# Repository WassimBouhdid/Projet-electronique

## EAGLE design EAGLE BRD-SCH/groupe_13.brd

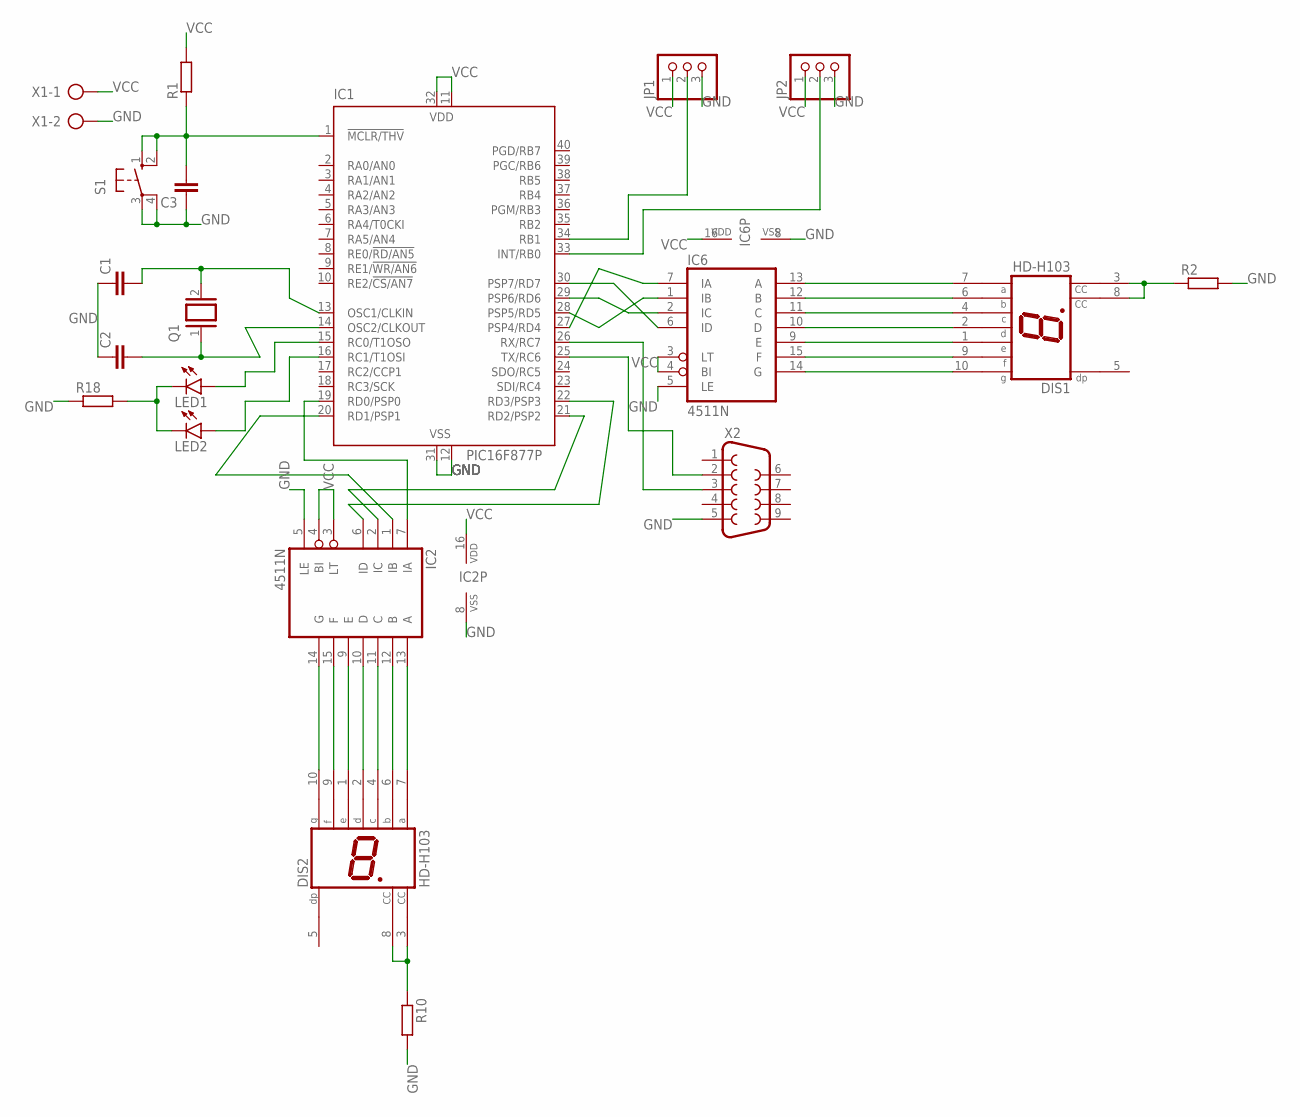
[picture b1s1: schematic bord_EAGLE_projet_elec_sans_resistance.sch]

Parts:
C1, C2: C-EU025-025X050; C025-025X050
C3: C-EU025-024X044; C025-024X044
DIS1, DIS2: HD-H103; HDSP-M
IC1: PIC16F877P; DIL40
IC2, IC6: 4511N; DIL16
JP1, JP2: PINHD-1X3; 1X03
LED1, LED2: LED5MM
Q1: XTAL/S; QS
R1, R2, R10, R18: R-EU_0204/7; 0204/7
S1: 10-XX; B3F-10XX
X1: AK300/2
X2: F09H

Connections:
GND: C1.1, C2.1, C3.1, IC1.12 (VSS), IC1.31 (VSS), IC2.5 (LE), IC2.8 (VSS), IC6.5 (LE), IC6.8 (VSS), JP1.3, JP2.3, R2.2, R10.2, R18.1, S1.3, S1.4 (P1), X1.2, X2.5
unnamed: C1.2, IC1.13 (OSC1/CLKIN), Q1.2
unnamed: C2.2, IC1.14 (OSC2/CLKOUT), Q1.1
unnamed: C3.2, IC1.1 (!MCLR/THV), R1.1, S1.1 (S), S1.2 (S1)
unnamed: IC1.19 (RD0/PSP0), IC2.7 (IA)
unnamed: IC1.20 (RD1/PSP1), IC2.1 (IB)
unnamed: IC1.21 (RD2/PSP2), IC2.2 (IC)
unnamed: IC1.22 (RD3/PSP3), IC2.6 (ID)
unnamed: IC1.27 (PSP4/RD4), IC6.7 (IA)
unnamed: IC1.28 (PSP5/RD5), IC6.1 (IB)
unnamed: IC1.29 (PSP6/RD6), IC6.2 (IC)
unnamed: IC1.30 (PSP7/RD7), IC6.6 (ID)
unnamed: DIS1.7 (A), IC6.13 (A)
unnamed: DIS1.6 (B), IC6.12 (B)
unnamed: DIS1.4 (C), IC6.11 (C)
unnamed: DIS1.2 (D), IC6.10 (D)
unnamed: DIS1.1 (E), IC6.9 (E)
unnamed: DIS1.9 (F), IC6.15 (F)
unnamed: DIS1.10 (G), IC6.14 (G)
unnamed: DIS2.10 (G), IC2.14 (G)
unnamed: DIS2.9 (F), IC2.15 (F)
unnamed: DIS2.1 (E), IC2.9 (E)
unnamed: DIS2.2 (D), IC2.10 (D)
unnamed: DIS2.4 (C), IC2.11 (C)
unnamed: DIS2.6 (B), IC2.12 (B)
unnamed: DIS2.7 (A), IC2.13 (A)
unnamed: DIS1.3 (CC), DIS1.8 (CC), R2.1
unnamed: DIS2.3 (CC), DIS2.8 (CC), R10.1
unnamed: IC1.15 (RC0/T1OSO), LED1.A
unnamed: IC1.16 (RC1/T1OSI), LED2.A
unnamed: LED1.K (C), LED2.K (C), R18.2
unnamed: IC1.25 (TX/RC6), X2.2
unnamed: IC1.26 (RX/RC7), X2.3
unnamed: IC1.33 (INT/RB0), JP2.2
unnamed: IC1.34 (RB1), JP1.2
VCC: IC1.11 (VDD), IC1.32 (VDD), IC2.3 (LT), IC2.4 (BI), IC2.16 (VDD), IC6.3 (LT), IC6.4 (BI), IC6.16 (VDD), JP1.1, JP2.1, R1.2, X1.1

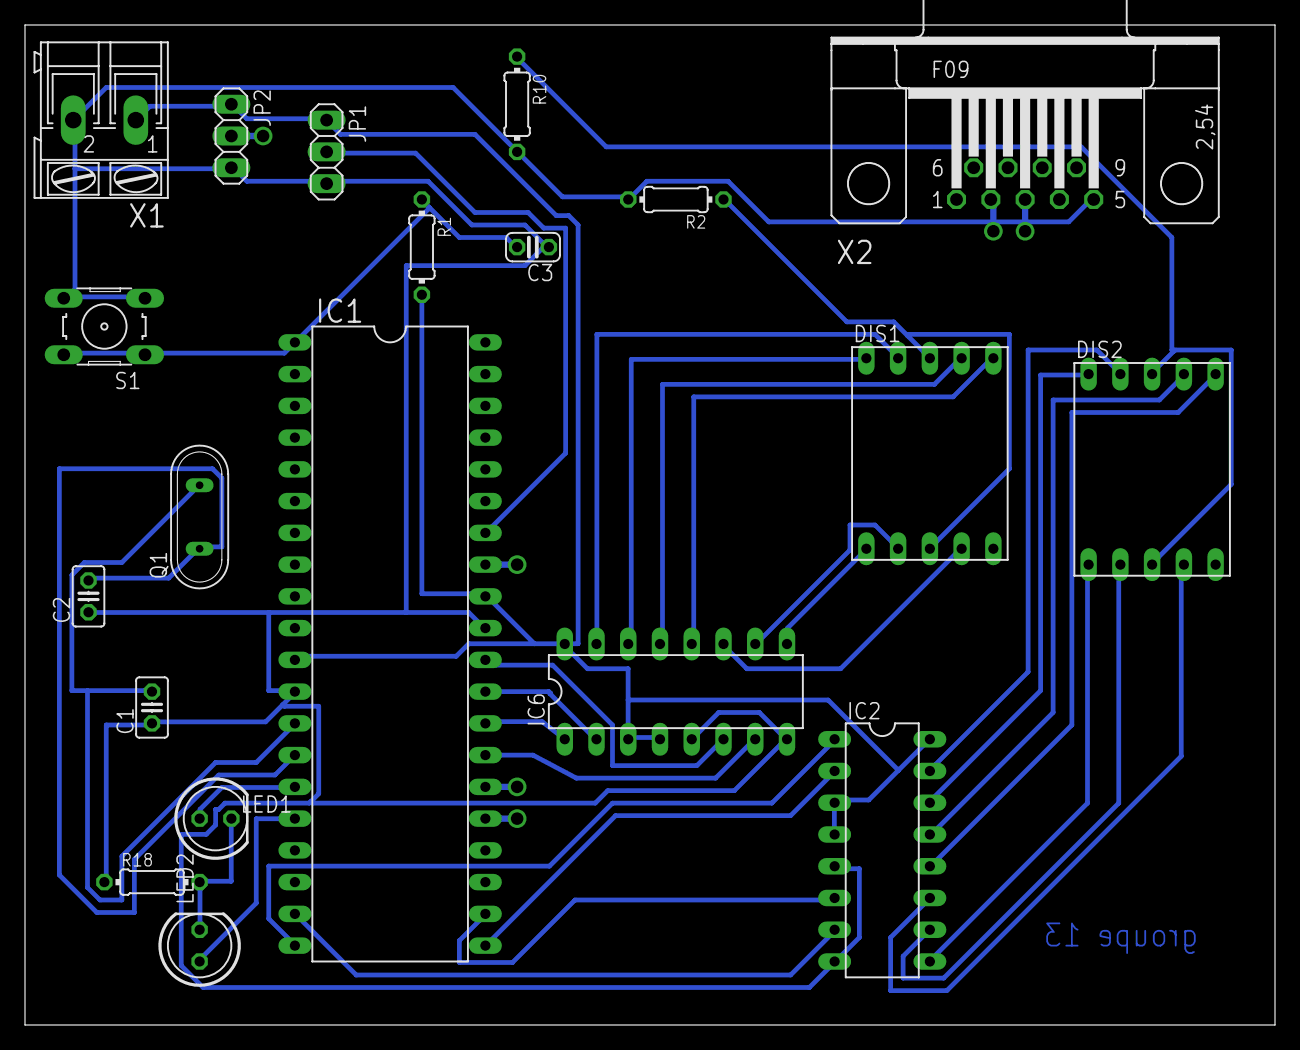
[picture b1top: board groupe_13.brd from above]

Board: 2 copper layers, 100.0 x 80.0 mm, 20 parts (0 on the bottom side), 36 nets.

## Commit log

2021-05-12 code C fonctionnel
2021-05-19 Code C
